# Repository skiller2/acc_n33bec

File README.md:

ESP32 Access Control Production Firmware

Features:
- Wiegand 26 input
- File-based storage (LittleFS)
- REST API
- WebSocket real-time
- Web dashboard
- OTA ready
- Ethernet connectivity
- WiFi with DPP Enrollee (Wi-Fi Easy Connect) provisioning

Build:
idf.py build
idf.py flash monitor

## WiFi DPP Provisioning

The device supports Device Provisioning Protocol (DPP) enrollee mode for
WiFi provisioning. When powered on, the device starts a DPP enrollee that
generates a QR code. Scan the QR code with a DPP configurator (e.g. Android
Wi-Fi Easy Connect) to provision WiFi credentials.

The DPP QR code and WiFi status are accessible via the HTTP API:
- `POST /dpp/bootstrap` - Regenerate the DPP bootstrap/QR code

WiFi status updates are pushed to the web dashboard via WebSocket broadcast.
The web dashboard also includes a WiFi/DPP tab that renders the QR code.

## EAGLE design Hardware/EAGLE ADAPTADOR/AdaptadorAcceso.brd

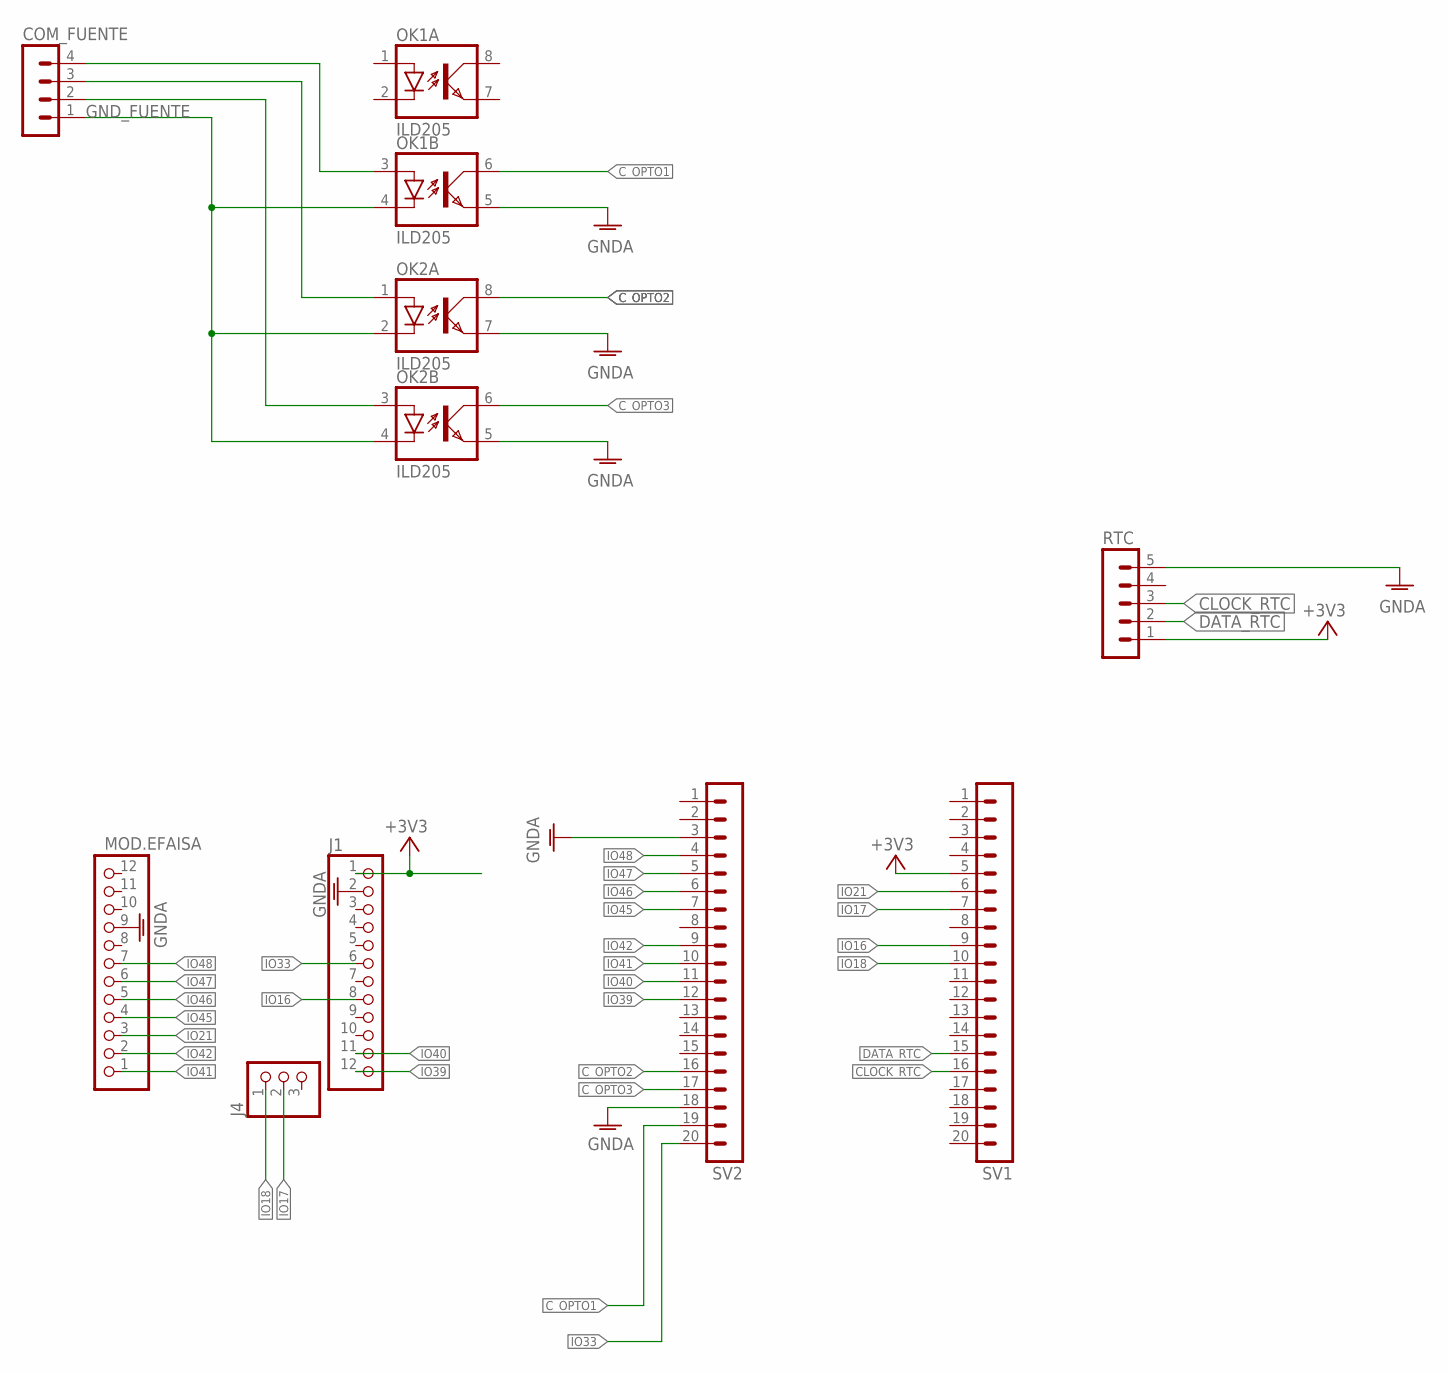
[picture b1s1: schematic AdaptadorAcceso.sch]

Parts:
COM_FUENTE: MA04-1
J1: PINHD-1X12; 1X12
J4: PINHD-1X3; 1X03
MOD.EFAISA: PINHD-1X12; 1X12
OK1, OK2: ILD205; SOIC08
RTC: MA05-1
SV1, SV2: MA20-1L

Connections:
+3V3: J1.1, RTC.1, SV1.5
CLOCK_RTC: RTC.3, SV1.16
C_OPTO1: OK1.6 (COL), SV2.19
C_OPTO2: OK2.8 (COL), SV2.16
C_OPTO3: OK2.6 (COL), SV2.17
DATA_RTC: RTC.2, SV1.15
GNDA: J1.2, MOD.EFAISA.9, OK1.5 (EMIT), OK2.5 (EMIT), OK2.7 (EMIT), RTC.5, SV2.3, SV2.18
GND_FUENTE: COM_FUENTE.1, OK1.4 (C), OK2.2 (C), OK2.4 (C)
IO16: J1.8, SV1.9
IO17: J4.2, SV1.7
IO18: J4.1, SV1.10
IO21: MOD.EFAISA.3, SV1.6
IO33: J1.6, SV2.20
IO39: J1.12, SV2.12
IO40: J1.11, SV2.11
IO41: MOD.EFAISA.1, SV2.10
IO42: MOD.EFAISA.2, SV2.9
IO45: MOD.EFAISA.4, SV2.7
IO46: MOD.EFAISA.5, SV2.6
IO47: MOD.EFAISA.6, SV2.5
IO48: MOD.EFAISA.7, SV2.4
unnamed: COM_FUENTE.4, OK1.3 (A)
unnamed: COM_FUENTE.3, OK2.1 (A)
unnamed: COM_FUENTE.2, OK2.3 (A)

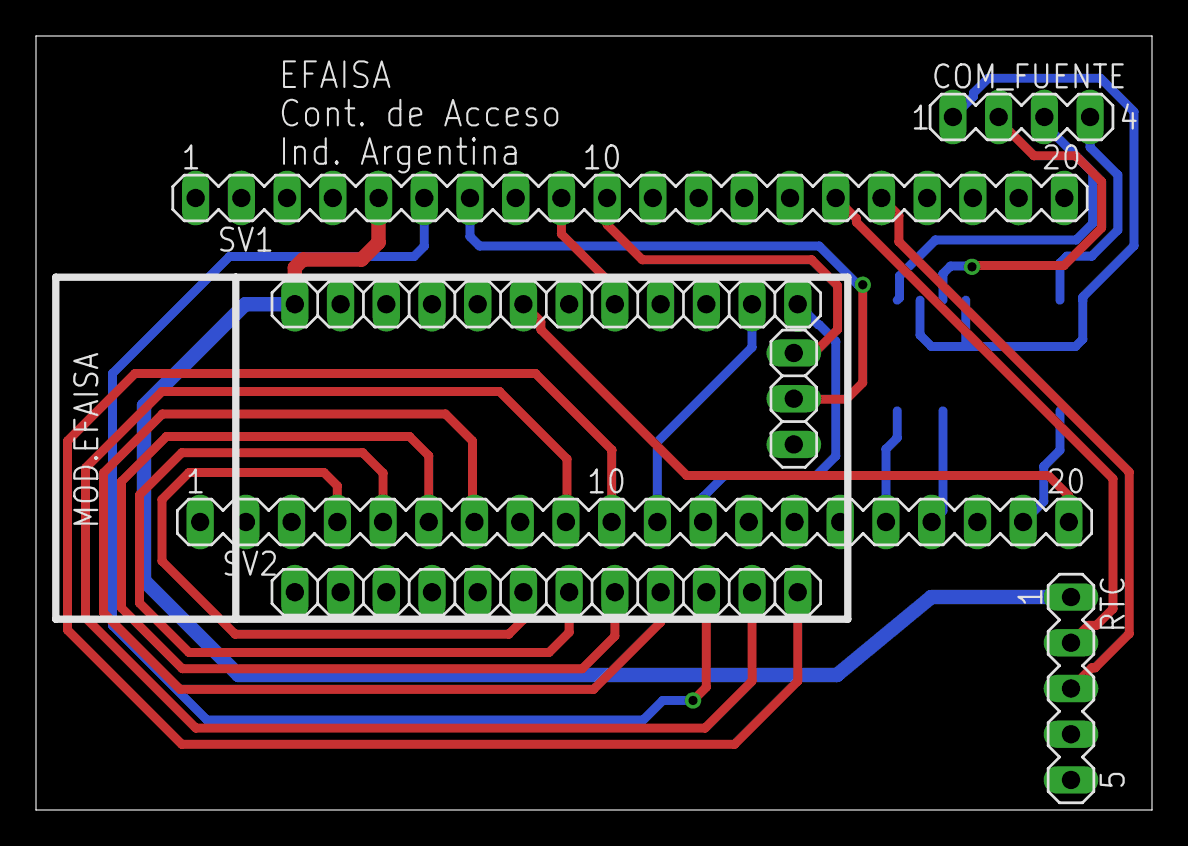
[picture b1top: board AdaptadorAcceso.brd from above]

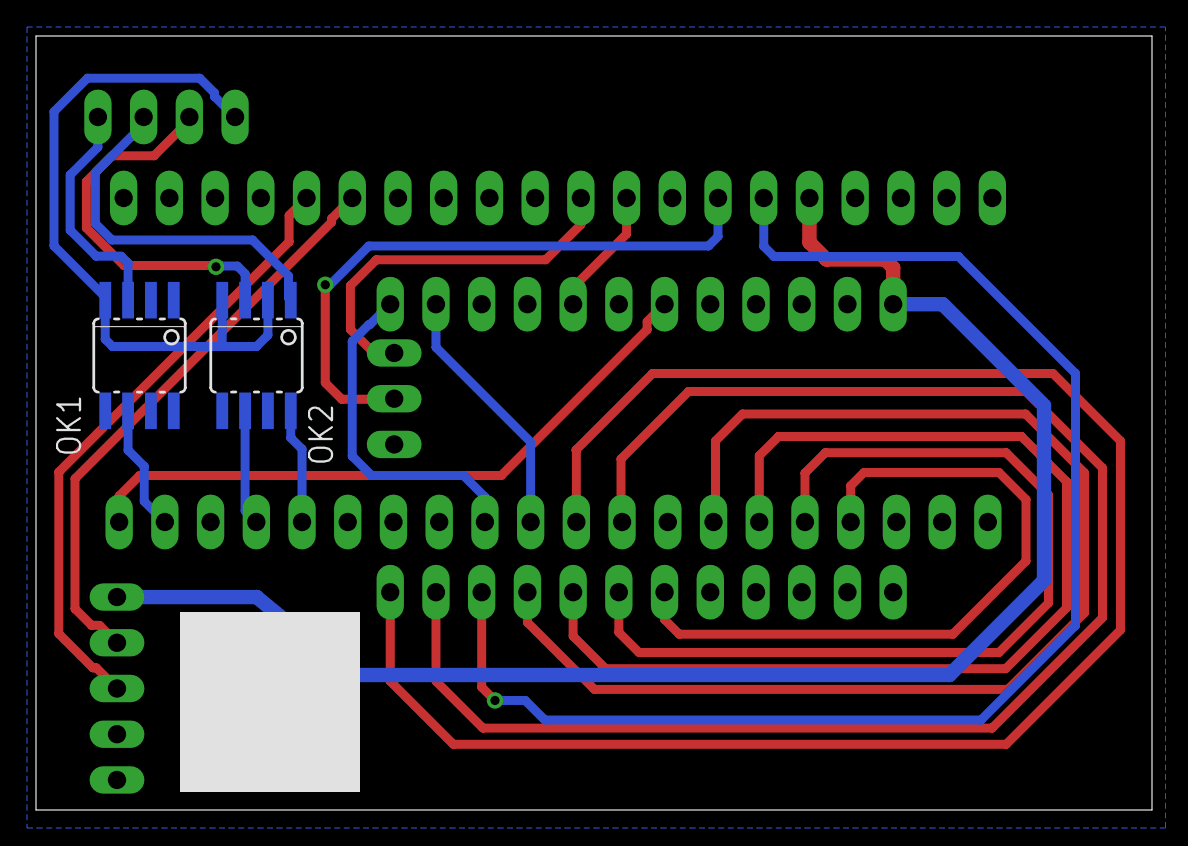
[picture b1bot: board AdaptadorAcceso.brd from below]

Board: 2 copper layers, 62.0 x 43.0 mm, 9 parts (2 on the bottom side), 24 nets.

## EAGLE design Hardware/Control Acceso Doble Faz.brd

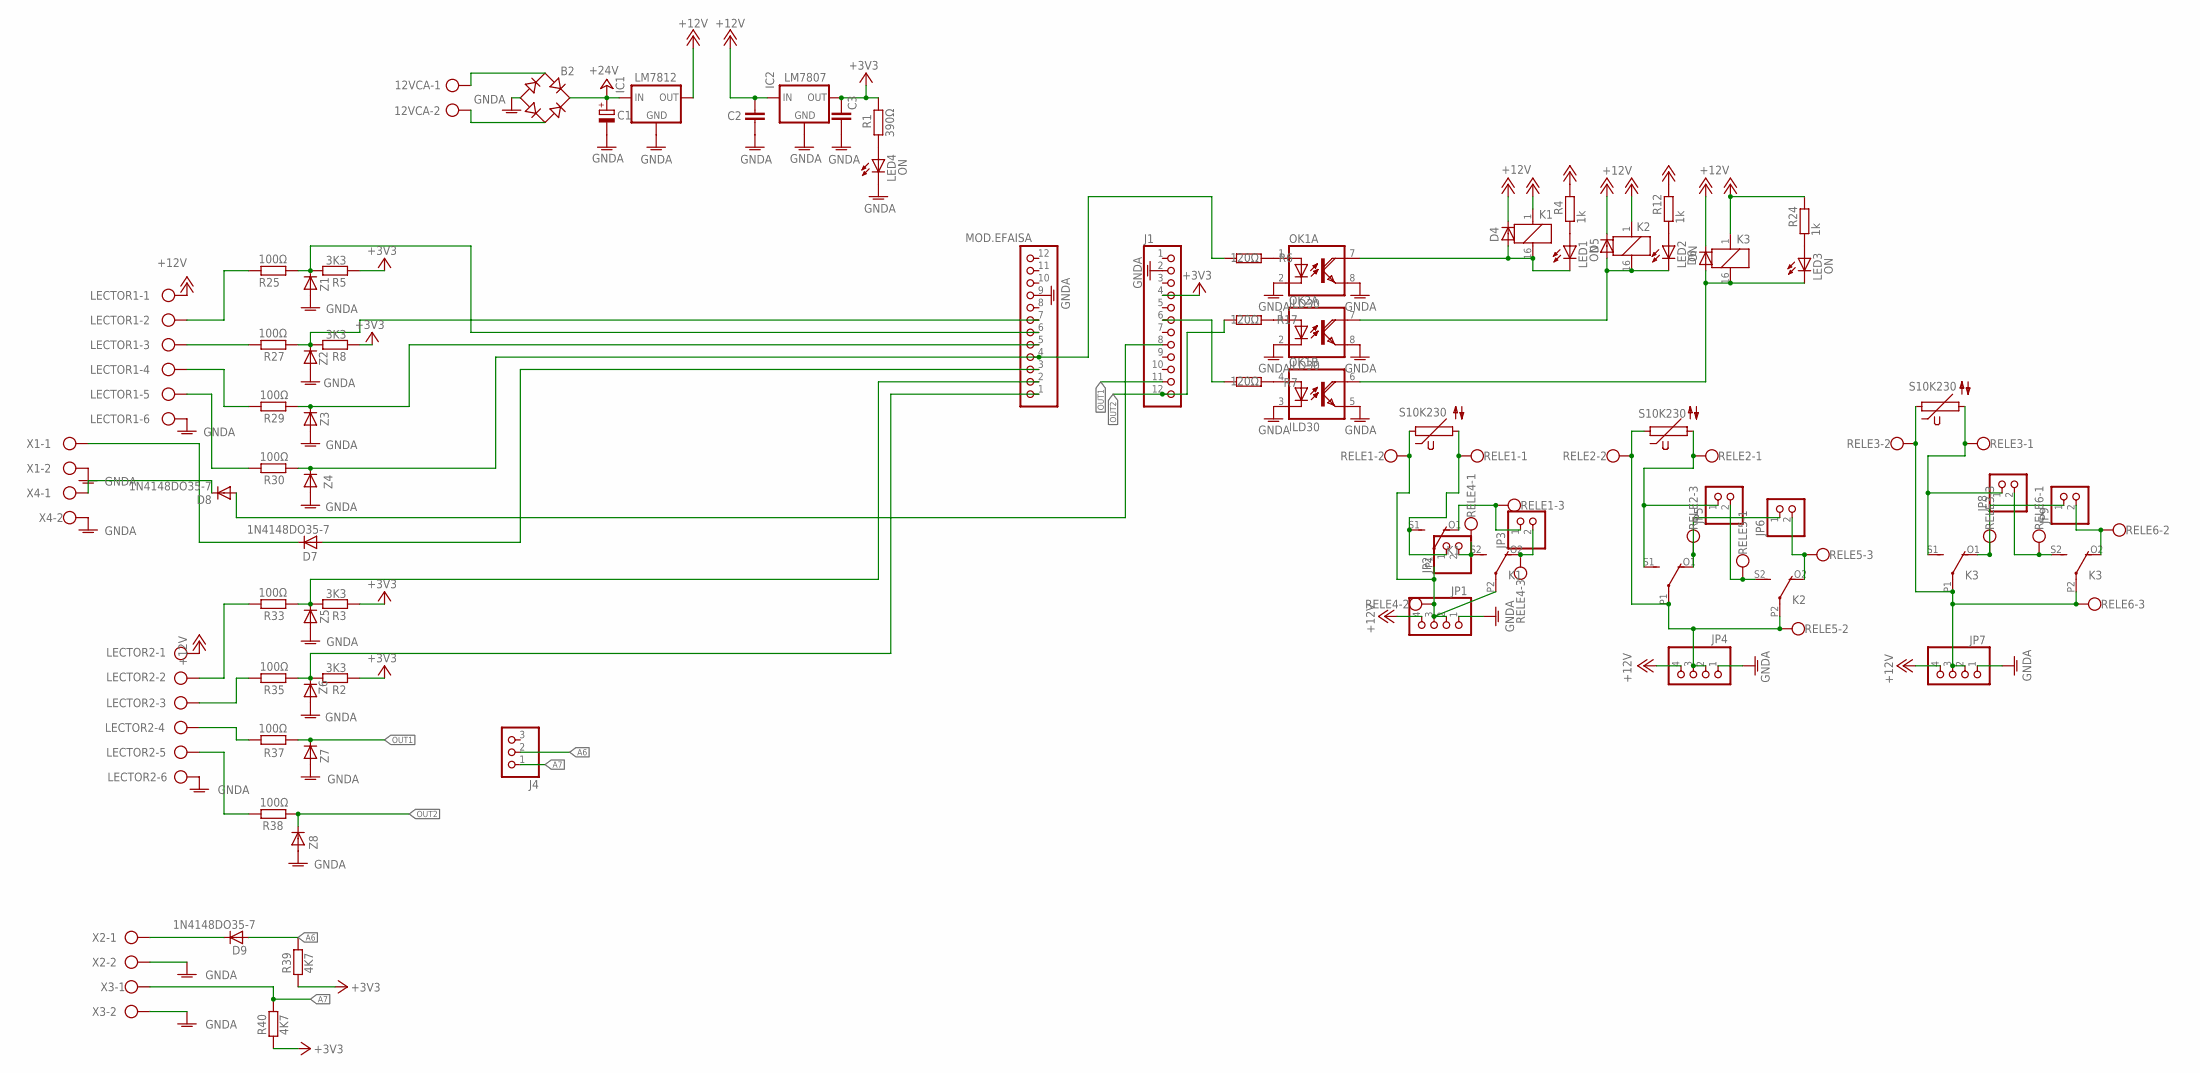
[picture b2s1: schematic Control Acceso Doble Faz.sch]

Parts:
12VCA: W237-102
B2: RB1A
C1: CPOL-EUE5-13; E5-13
C2, C3: C-EU050-024X044; C050-024X044
D4, D5, D6, D7, D8, D9: 1N4148DO35-7; DO35-7
IC1: LM7812; 78XXS
IC2: LM7807; 78XXS
J1: PINHD-1X12; 1X12
J4: PINHD-1X3; 1X03
JP1, JP4, JP7: PINHD-1X4; 1X04
JP2, JP3, JP5, JP6, JP8, JP9: PINHD-1X2; 1X02
K1, K2, K3: 351
LECTOR1, LECTOR2: W237-6
LED1, LED2, LED3, LED4: ON; LED3MM
MOD.EFAISA: PINHD-1X12; 1X12
OK1, OK2: ILD30; DIL08
R1: 390Ω; 0204/7
R2, R3, R5, R8: 3K3; 0204/7
R4, R12, R24: 1k; 0204/7
R6, R7, R17: 120Ω; 0204/7
R25, R27, R29, R30, R33, R35, R37, R38: 100Ω; 0204/7
R39, R40: 4K7; 0204/7
RELE1, RELE2, RELE3, RELE4, RELE5, RELE6: W237-103
V1, V2, V3: S10K230
X1, X2, X3, X4: W237-102
Z1, Z2, Z3, Z4, Z5, Z6, Z7, Z8: ZENNER 4V7; DO35-7

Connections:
+3V3: C3.1, IC2.OUT, J1.4, R1.2, R2.1, R3.1, R5.1, R8.1, R39.1, R40.1
+12V: C2.1, D4.C, D5.C, D6.C, IC1.OUT, IC2.IN, JP1.4, JP4.4, JP7.4, K1.1, K2.1, K3.1, LECTOR1.1, LECTOR2.1, R4.2, R12.2, R24.2
+24V: B2.+, C1.+, IC1.IN
A6: D9.A, J4.2, R39.2
A7: J4.1, R40.2, X3.1
GNDA: B2.-, C1.-, C2.2, C3.2, IC1.GND, IC2.GND, J1.2, JP1.1, JP4.1, JP7.1, LECTOR1.6, LECTOR2.6, LED4.K (C), MOD.EFAISA.9, OK1.2 (C), OK1.3 (C), OK1.5 (EMI), OK1.8 (EMI), OK2.2 (C), OK2.8 (EMI), X1.2, X2.2, X3.2, X4.2, Z1.A, Z2.A, Z3.A, Z4.A, Z5.A, Z6.A, Z7.A, Z8.A
unnamed: 12VCA.1, B2.AC1
unnamed: 12VCA.2, B2.AC2
unnamed: MOD.EFAISA.4, R6.2, R30.1, Z4.C
unnamed: MOD.EFAISA.6, R5.2, R25.1, Z1.C
unnamed: D7.A, MOD.EFAISA.3
unnamed: J1.6, R7.2
unnamed: OK1.1 (A), R6.1
unnamed: OK2.1 (A), R17.1
unnamed: MOD.EFAISA.7, R8.2, R27.1, Z2.C
unnamed: OK1.4 (A), R7.1
unnamed: D4.A, K1.16 (2), LED1.K (C), OK1.7 (COL)
unnamed: D5.A, K2.16 (2), LED2.K (C), OK2.7 (COL)
unnamed: D6.A, K3.16 (2), LED3.K (C), OK1.6 (COL)
unnamed: JP9.1, K3.O1 (O), RELE3.3
unnamed: LECTOR1.2, R25.2
unnamed: LECTOR1.3, R27.2
unnamed: MOD.EFAISA.5, R29.1, Z3.C
unnamed: MOD.EFAISA.2, R3.2, R33.1, Z5.C
unnamed: LECTOR1.4, R29.2
unnamed: LECTOR2.2, R33.2
unnamed: MOD.EFAISA.1, R2.2, R35.1, Z6.C
unnamed: LECTOR1.5, R30.2
unnamed: D7.C, X1.1
unnamed: LECTOR2.3, R35.2
unnamed: LECTOR2.4, R37.2
unnamed: LED4.A, R1.1
unnamed: JP6.1, K2.O1 (O), RELE2.3
unnamed: JP2.2, K1.S2 (S), RELE4.1
unnamed: JP3.2, K1.O2 (O), RELE4.3
unnamed: JP3.1, K1.O1 (O), RELE1.3
unnamed: LED3.A, R24.1
unnamed: JP6.2, K2.O2 (O), RELE5.3
unnamed: JP7.2, JP7.3, K3.P1, K3.P2, RELE3.2, RELE6.3, V3.1
unnamed: LECTOR2.5, R38.2
unnamed: D9.C, X2.1
unnamed: JP5.2, K2.S2 (S), RELE5.1
unnamed: JP8.2, K3.S2 (S), RELE6.1
unnamed: LED2.A, R12.1
unnamed: LED1.A, R4.1
unnamed: JP1.2, JP1.3, K1.P1, K1.P2, RELE1.2, RELE4.2, V1.1
unnamed: JP2.1, K1.S1 (S), RELE1.1, V1.2
unnamed: JP9.2, K3.O2 (O), RELE6.2
unnamed: JP5.1, K2.S1 (S), RELE2.1, V2.2
unnamed: JP4.2, JP4.3, K2.P1, K2.P2, RELE2.2, RELE5.2, V2.1
unnamed: JP8.1, K3.S1 (S), RELE3.1, V3.2
unnamed: D8.A, J1.8
unnamed: D8.C, X4.1
OUT1: J1.11, R37.1, Z7.C
OUT2: J1.12, R17.2, R38.1, Z8.C

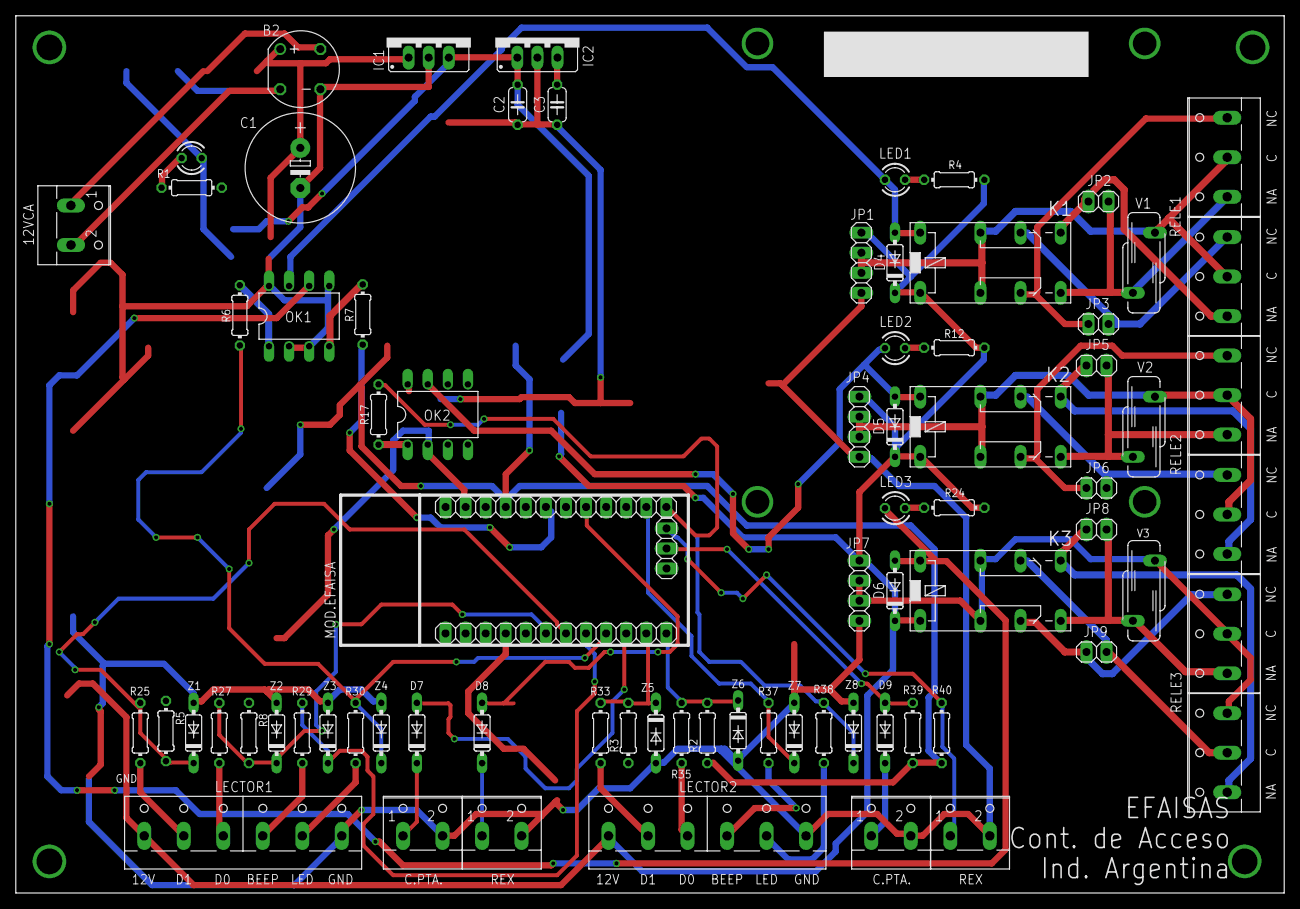
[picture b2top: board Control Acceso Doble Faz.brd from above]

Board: 2 copper layers, 160.5 x 111.0 mm, 78 parts (0 on the bottom side), 55 nets.

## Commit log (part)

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2026-05-15 Initial
2026-05-15 Now it´s compiling
2026-05-15 Fix versions
2026-05-15 Update api
2026-05-15 Fix partition
2026-05-15 Add Circular limit
2026-05-16 Got IP
2026-05-16 add header to log_store
2026-05-16 Add sntp time sync
2026-05-16 Correct Wiegand reader
2026-05-16 add lib wiegand
2026-05-23 Add dual wiegand reader
2026-05-23 working
2026-05-23 Add async version
2026-05-30 Add config vars
2026-05-30 Add web page
2026-05-30 List files on init
2026-05-30 Fix storage partition
2026-05-30 Change data gpios reader 2
2026-05-30 Add global config
2026-05-30 Add missing functions loadLogs & loadCards
2026-06-06 Add first version of RTC
2026-06-06 fix rtc logic
2026-06-13 Fix Wiegand Decoder
2026-06-16 Add power events
2026-06-27 Board
2026-06-27 Esquematico completo - A revisar
2026-06-27 Inicio de routeo
2026-06-29 PCB terminado - A revisar
2026-06-29 Actualizacion PCB - A revisar
